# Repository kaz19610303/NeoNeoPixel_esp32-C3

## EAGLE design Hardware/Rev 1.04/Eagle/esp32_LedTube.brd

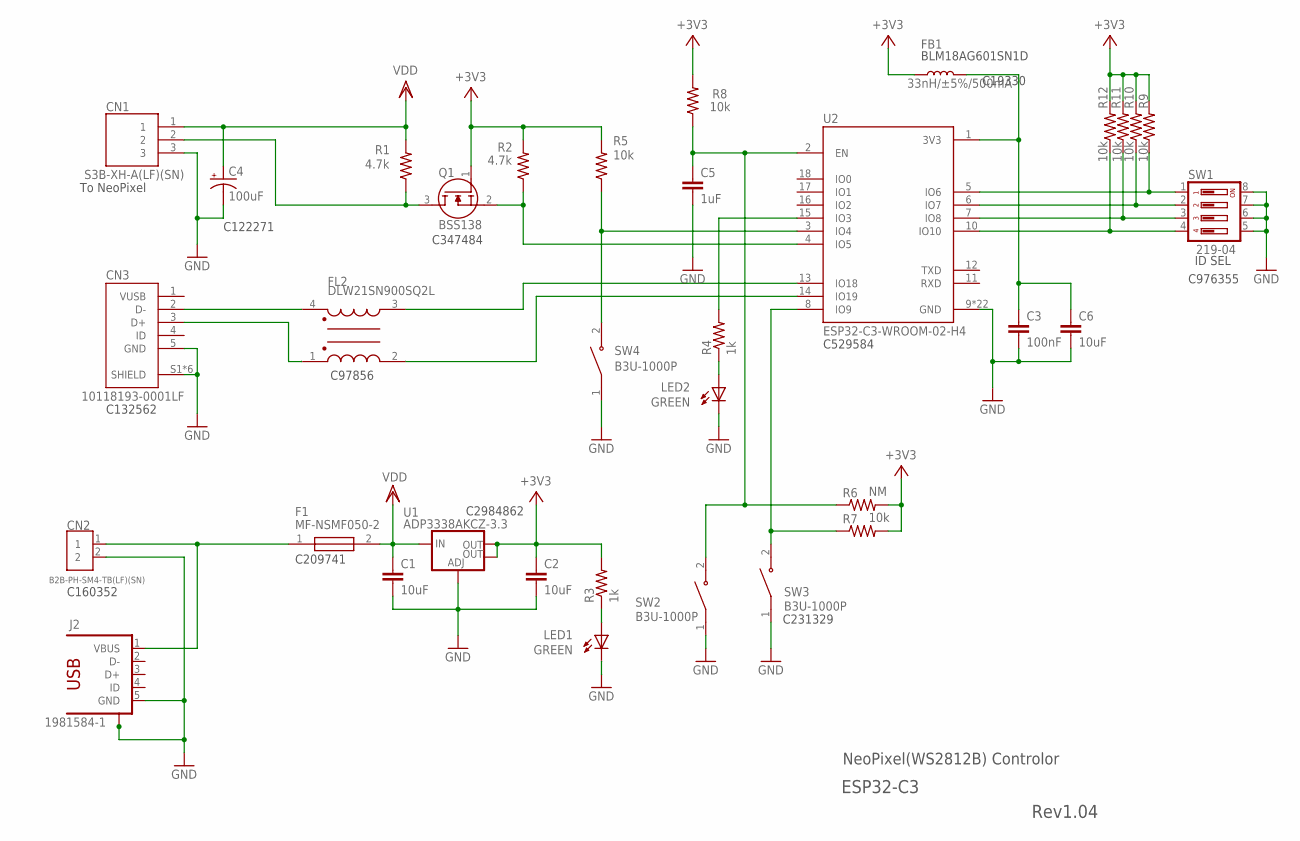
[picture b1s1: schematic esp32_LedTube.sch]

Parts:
C1, C2, C6: 10uF; C0603
C3: 100nF; C0603
C4: 100uF; B/3528-21R
C5: 1uF; C0603
CN1: S3B-XH-A(LF)(SN); JST_S3B-XH-A(LF)(SN)
CN2: B2B-PH-SM4-TB(LF)(SN); JST_B2B-PH-SM4-TB(LF)(SN)
CN3: 10118193-0001LF; FCI_10118193-0001LF
F1: MF-NSMF050-2; FUSC3216X85N
FB1: 33nH/±5%/500mA; 0603
FL2: DLW21SN900SQ2L; FIL_DLW21SN900SQ2L
J2: 1981584-1; MPN ZX62-AB-5PA(11)
LED1, LED2: GREEN; CHIPLED_0603
Q1: BSS138; SOT95P240X120-3N
R1, R2: 4.7k; 0603
R3, R4: 1k; R0603
R5, R7, R8, R9, R10, R11, R12: 10k; R0603
R6: NM; R0603
SW1: 219-04; CTS-219-04
SW2, SW3, SW4: B3U-1000P; SW_B3U-1000P
U1: ADP3338AKCZ-3.3; SOT223
U2: ESP32-C3-WROOM-02-H4; MODULE_ESP32-C3-WROOM-02-H4

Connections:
+3V3: C2.1, FB1.1, Q1.1 (G), R2.2, R3.2, R5.2, R6.2, R7.2, R8.2, R9.2, R10.2, R11.2, R12.2, U1.2 (OUT), U1.4 (OUT)
GND: C1.2, C2.2, C3.2, C4.-, C5.2, C6.2, CN1.3, CN2.2, CN3.5 (GND), CN3.S1 (SHIELD), CN3.S2 (SHIELD), CN3.S3 (SHIELD), CN3.S4 (SHIELD), CN3.S5 (SHIELD), CN3.S6 (SHIELD), J2.5 (GND), J2.S1, J2.S2, J2.S3, J2.S4, LED1.C, LED2.C, SW1.5, SW1.6, SW1.7, SW1.8, SW2.1, SW3.1, SW4.1, U1.1 (ADJ), U2.9 (GND), U2.19 (GND), U2.20 (GND), U2.21 (GND), U2.22 (GND), U2.23 (GND), U2.24 (GND), U2.25 (GND), U2.26 (GND), U2.27 (GND), U2.28 (GND), U2.29 (GND), U2.30 (GND), U2.31 (GND), U2.32 (GND), U2.33 (GND), U2.34 (GND), U2.35 (GND), U2.36 (GND), U2.37 (GND), U2.38 (GND), U2.39 (GND)
IO4: R9.1, SW1.1, U2.5 (IO6)
IO12: R10.1, SW1.2, U2.6 (IO7)
IO13: R11.1, SW1.3, U2.7 (IO8)
IO14: R12.1, SW1.4, U2.10 (IO10)
unnamed: CN1.2, Q1.3 (D), R1.1
unnamed: LED2.A, R4.1
unnamed: FL2.3, U2.13 (IO18)
unnamed: R5.1, SW4.2, U2.3 (IO4)
unnamed: CN2.1, F1.1, J2.1 (VBUS)
unnamed: CN3.2 (D-), FL2.4
unnamed: CN3.3 (D+), FL2.1
unnamed: FL2.2, U2.14 (IO19)
unnamed: R4.2, U2.15 (IO3)
unnamed: LED1.A, R3.1
unnamed: R7.1, SW3.2, U2.8 (IO9)
unnamed: C3.1, C6.1, FB1.2, U2.1 (3V3)
RST: C5.1, R6.1, R8.1, SW2.2, U2.2 (EN)
SCL_18: Q1.2 (S), R2.1, U2.4 (IO5)
VDD: C1.1, C4.+, CN1.1, F1.2, R1.2, U1.3 (IN)

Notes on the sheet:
ID SEL
NeoPixel(WS2812B) Controlor
C529584
C347484
C976355
C122271
C209741
To NeoPixel
C132562
C160352
C231329
C2984862
ESP32-C3
Rev1.04
C19330
BLM18AG601SN1D
C97856

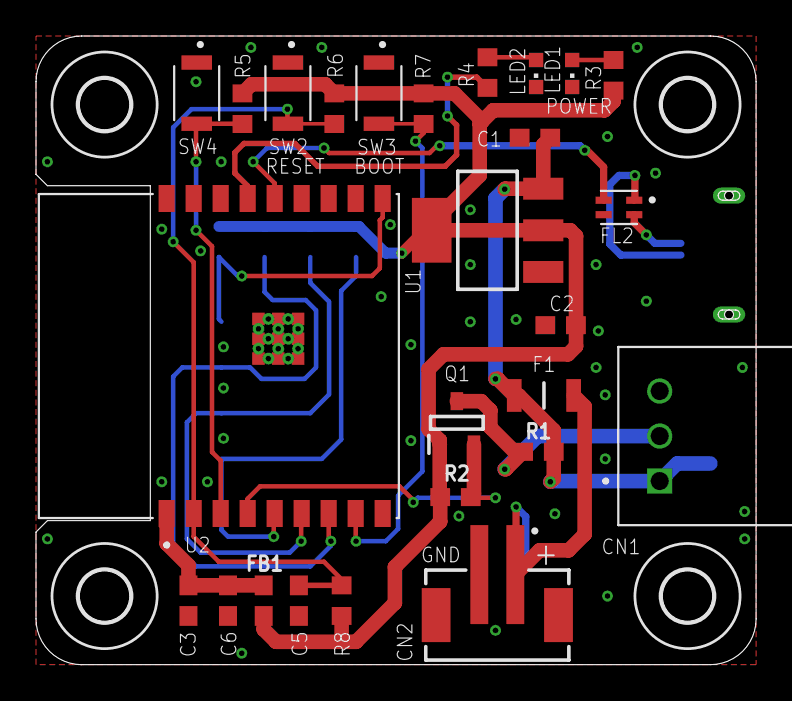
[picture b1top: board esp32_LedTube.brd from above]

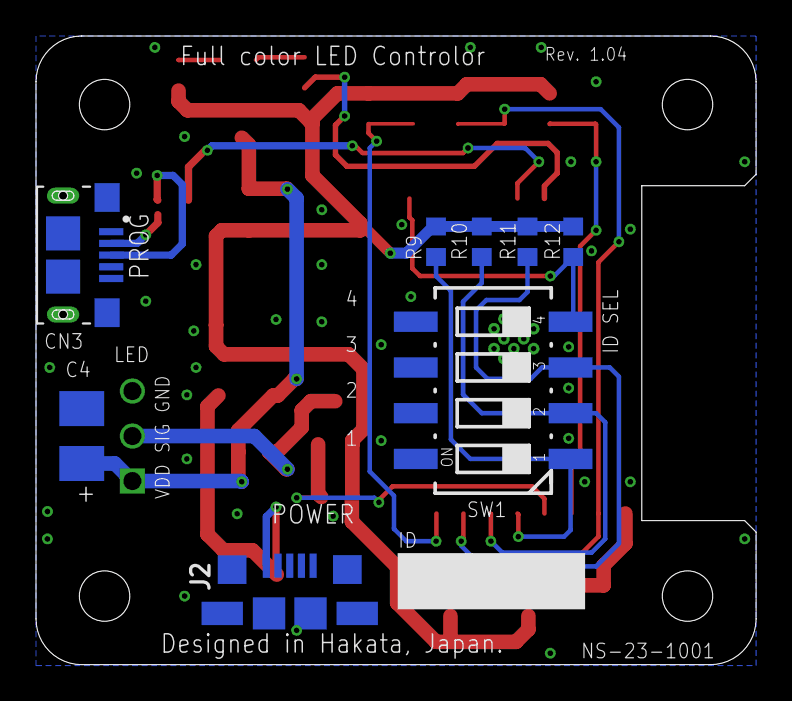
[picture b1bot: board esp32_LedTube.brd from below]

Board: 2 copper layers, 40.0 x 34.9 mm, 38 parts (8 on the bottom side), 21 nets.

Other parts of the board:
U$1, U$2, U$3, U$4: 2,8

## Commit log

2023-02-10 Heardware document upload.
2023-02-10 BOM list upload.

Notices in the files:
parts and their libraries:
SparkFun-Coils: Licensing: Creative Commons ShareAlike 4.0 International - https://creativecommons.org/licenses/by-sa/4.0
con-usb: Copyright (C) 2008, Bob Starr
